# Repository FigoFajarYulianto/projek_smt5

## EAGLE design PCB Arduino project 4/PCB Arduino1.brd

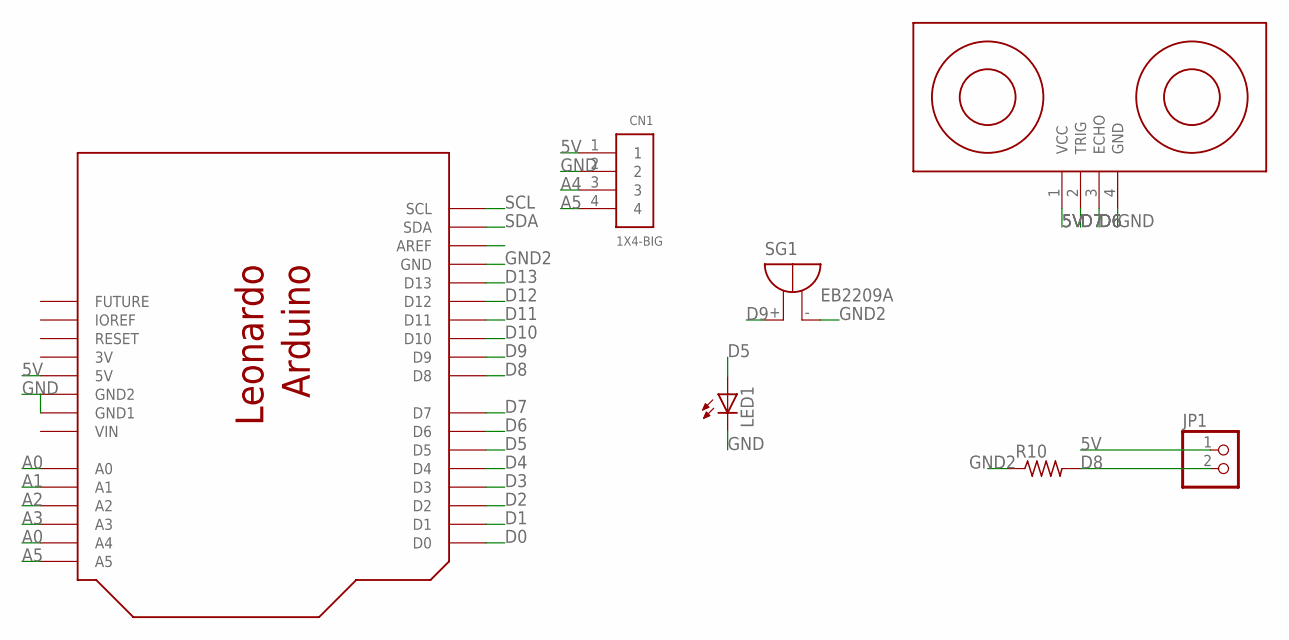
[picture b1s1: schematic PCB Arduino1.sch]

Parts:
CN1: 1X4-BIG; 1X04-BIG
JP1: PINHD-1X2; 1X02
LED1: LEDB152; Q62902-B152
R10: R-US_0204/7; 0204/7
SG1: EB2209A
U$1: ARDUINO_LEONARDO
U$2: ULTRASONIC-HC-SR04

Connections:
3V: U$1.3V
5V: CN1.1, JP1.1, U$1.5V, U$2.1 (VCC)
A0: U$1.A0
A1: U$1.A1
A2: U$1.A2
A3: U$1.A3
A4: CN1.3, U$1.A4
A5: CN1.4, U$1.A5
D0: U$1.D0
D1: U$1.D1
D2: U$1.D2
D3: U$1.D3
D4: U$1.D4
D5: LED1.A, U$1.D5
D6: U$1.D6, U$2.3 (ECHO)
D7: U$1.D7, U$2.2 (TRIG)
D8: JP1.2, R10.2, U$1.D8
D9: SG1.+, U$1.D9
D10: U$1.D10
D11: U$1.D11
D12: U$1.D12
D13: U$1.D13
GND: CN1.2, LED1.K (C), U$1.GND$2 (GND2), U$1.GND$3 (GND1), U$2.4 (GND)
GND2: R10.1, SG1.-, U$1.GND
SCL: U$1.SCL
SDA: U$1.SDA
VIN: U$1.VIN

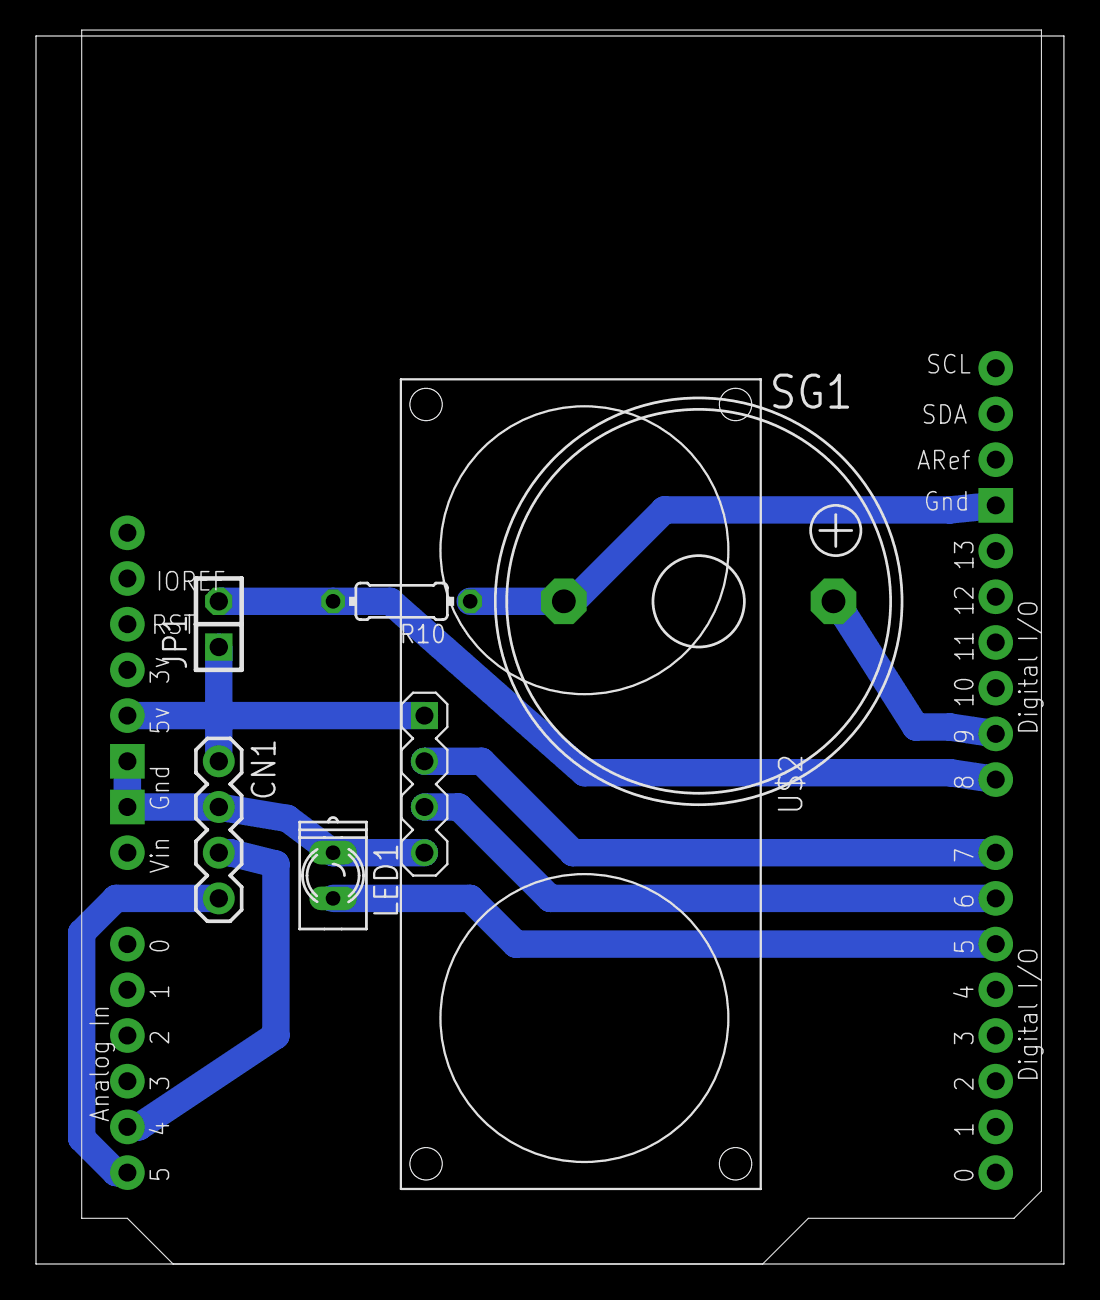
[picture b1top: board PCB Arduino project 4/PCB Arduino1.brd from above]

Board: 2 copper layers, 57.1 x 68.2 mm, 7 parts (0 on the bottom side), 10 nets.

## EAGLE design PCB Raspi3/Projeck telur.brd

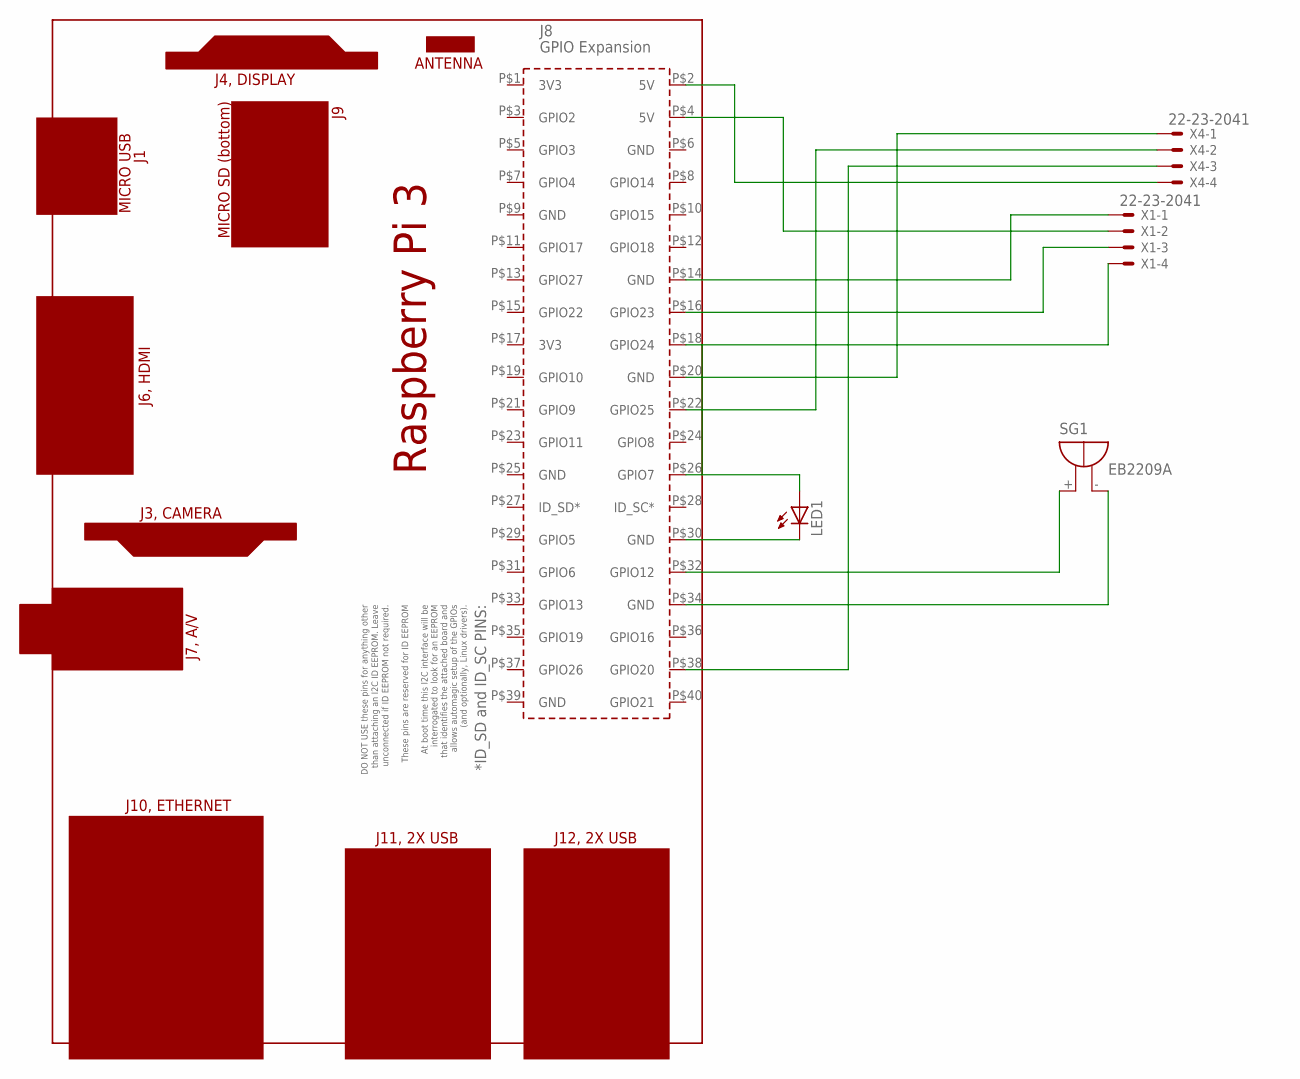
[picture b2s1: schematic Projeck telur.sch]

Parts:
LED1: LEDB152; Q62902-B152
PCB1: RPI3
SG1: EB2209A
X1, X4: 22-23-2041

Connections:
unnamed: PCB1.P$14 (GND), X1.1
unnamed: PCB1.P$4 (5V), X1.2
unnamed: PCB1.P$38 (GPIO20), X4.3
unnamed: PCB1.P$2 (5V), X4.4
unnamed: PCB1.P$22 (GPIO25), X4.2
unnamed: PCB1.P$20 (GND), X4.1
unnamed: PCB1.P$32 (GPIO12), SG1.+
unnamed: LED1.A, PCB1.P$26 (GPIO7)
unnamed: LED1.K (C), PCB1.P$30 (GND)
unnamed: PCB1.P$16 (GPIO23), X1.3
unnamed: PCB1.P$18 (GPIO24), X1.4
unnamed: PCB1.P$34 (GND), SG1.-

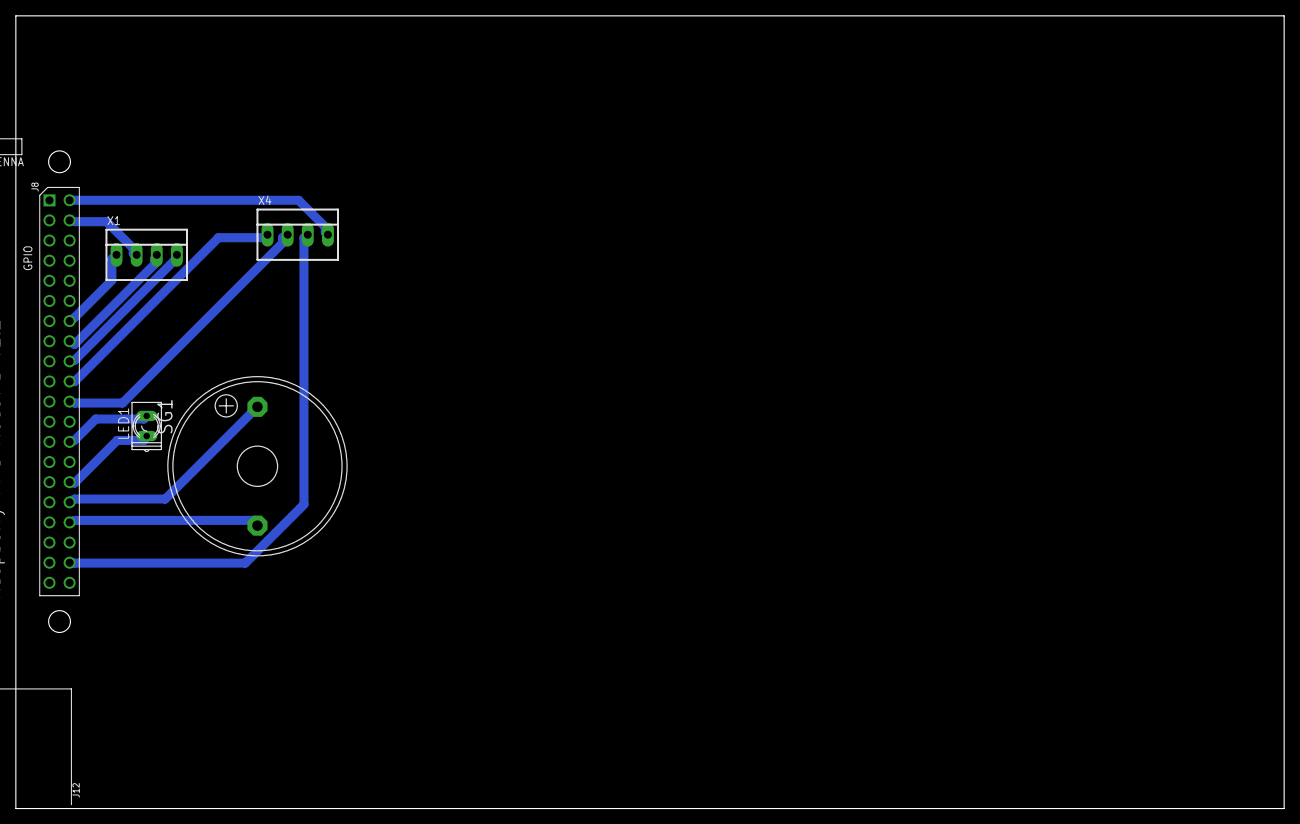
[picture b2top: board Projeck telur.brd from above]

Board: 2 copper layers, 160.0 x 100.0 mm, 5 parts (0 on the bottom side), 12 nets.

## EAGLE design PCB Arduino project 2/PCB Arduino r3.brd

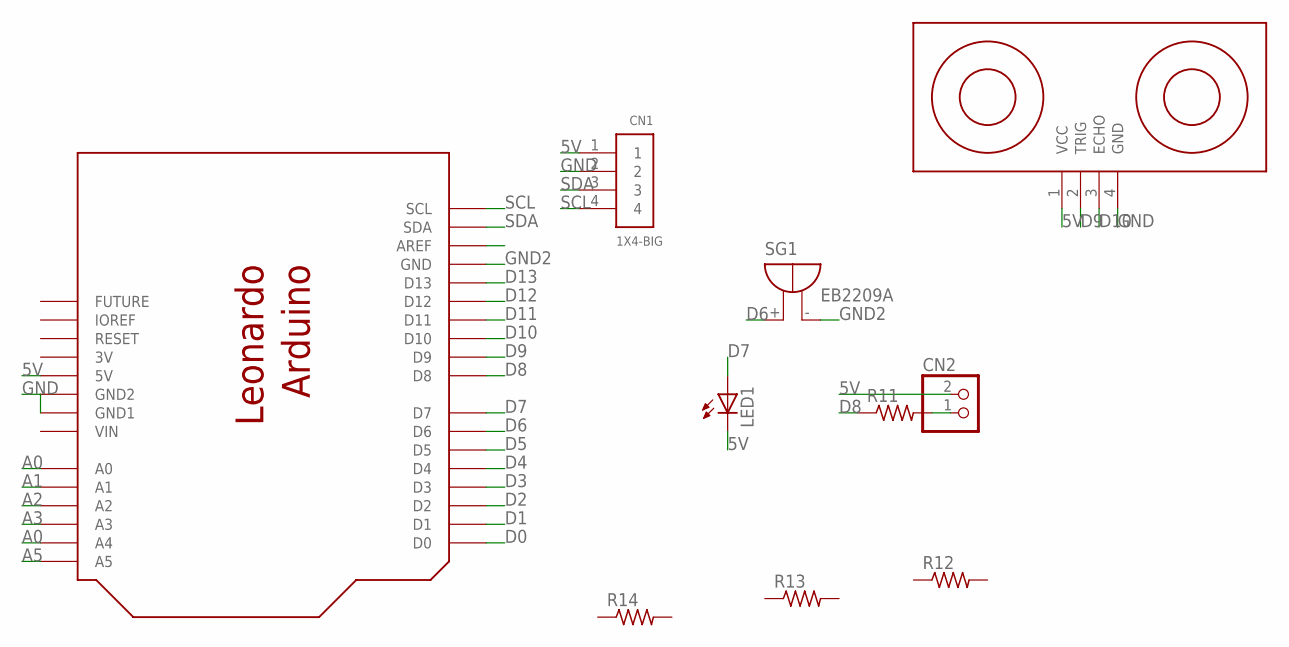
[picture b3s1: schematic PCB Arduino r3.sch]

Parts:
CN1: 1X4-BIG; 1X04-BIG
CN2: JST_2PIN-THM; JST-PH-2-THM
LED1: LEDB152; Q62902-B152
R11, R12, R13, R14: R-US_0204/7; 0204/7
SG1: EB2209A
U$1: ARDUINO_LEONARDO
U$2: ULTRASONIC-HC-SR04

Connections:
3V: U$1.3V
5V: CN1.1, CN2.2 (1), LED1.K (C), U$1.5V, U$2.1 (VCC)
A0: U$1.A0
A1: U$1.A1
A2: U$1.A2
A3: U$1.A3
A4: U$1.A4
A5: U$1.A5
D0: U$1.D0
D1: U$1.D1
D2: U$1.D2
D3: U$1.D3
D4: U$1.D4
D5: U$1.D5
D6: SG1.+, U$1.D6
D7: LED1.A, U$1.D7
D8: R11.1, U$1.D8
D9: U$1.D9, U$2.2 (TRIG)
D10: U$1.D10, U$2.3 (ECHO)
D11: U$1.D11
D12: U$1.D12
D13: U$1.D13
GND: CN1.2, U$1.GND$2 (GND2), U$1.GND$3 (GND1), U$2.4 (GND)
GND2: SG1.-, U$1.GND
unnamed: CN2.1 (2), R11.2
SCL: CN1.4, U$1.SCL
SDA: CN1.3, U$1.SDA
VIN: U$1.VIN

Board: 2 copper layers, 10 parts (0 on the bottom side), 11 nets, no tracks yet.

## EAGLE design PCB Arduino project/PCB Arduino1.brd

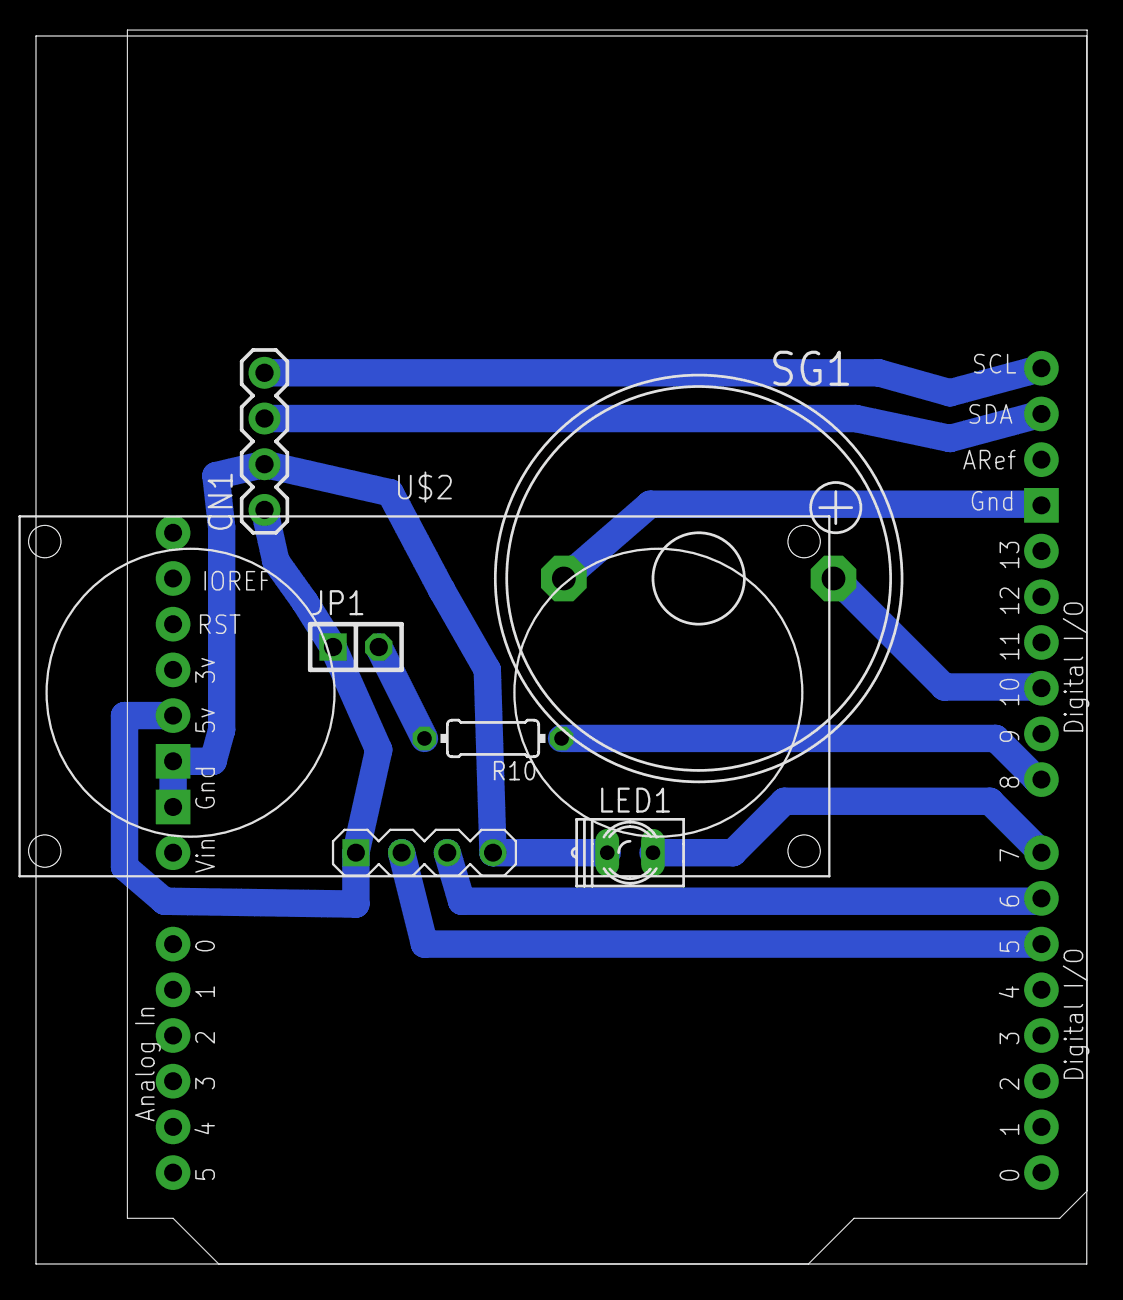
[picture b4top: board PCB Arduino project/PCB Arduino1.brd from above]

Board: 2 copper layers, 58.4 x 68.2 mm, 7 parts (0 on the bottom side), 11 nets.

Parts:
CN1: 1X4-BIG; 1X04-BIG
JP1: 1X02
LED1: Q62902-B152
R10: 0204/7
SG1: EB2209A
U$1: ARDUINO_LEONARDO
U$2: ULTRASONIC-HC-SR04

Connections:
5V: CN1.1, JP1.1, U$1.5V, U$2.1
D5: U$1.D5, U$2.2
D6: U$1.D6, U$2.3
D7: LED1.A, U$1.D7
D8: R10.1, U$1.D8
D10: SG1.+, U$1.D10
GND: CN1.2, LED1.K, U$1.GND$2, U$1.GND$3, U$2.4
GND2: SG1.-, U$1.GND
unnamed: JP1.2, R10.2
SCL: CN1.4, U$1.SCL
SDA: CN1.3, U$1.SDA

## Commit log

2021-12-12 tertanam
2021-12-15 design 3D
2021-12-22 image processing

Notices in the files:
parts and their libraries:
diy-modules: Released under the Creative Commons Attribution 4.0 International License: http://creativecommons.org/licenses/by/4.0
